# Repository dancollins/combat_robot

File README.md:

## Firmware

### Prerequisites

1. [Miniconda](https://docs.anaconda.com/miniconda/), and an environment with Python 3.10
2. [Zephyr SDK](https://docs.zephyrproject.org/latest/develop/toolchains/zephyr_sdk.html)
3. [CMake](https://cmake.org/download/)
4. [Ninja](https://ninja-build.org/)

Now you can run a few commands to get more dependancies:

    cd <repo>/zephyr-workspace
    west update
    cd zephyr/scripts
    pip install -r requirements.txt
    cd <repo>/zephyr-workspace

### Building

There's no actual firmware or board yet - so in the mean time here's a generic
build for the included minimal sample.

    west build --pristine --board nucleo_l412rb_p firmware

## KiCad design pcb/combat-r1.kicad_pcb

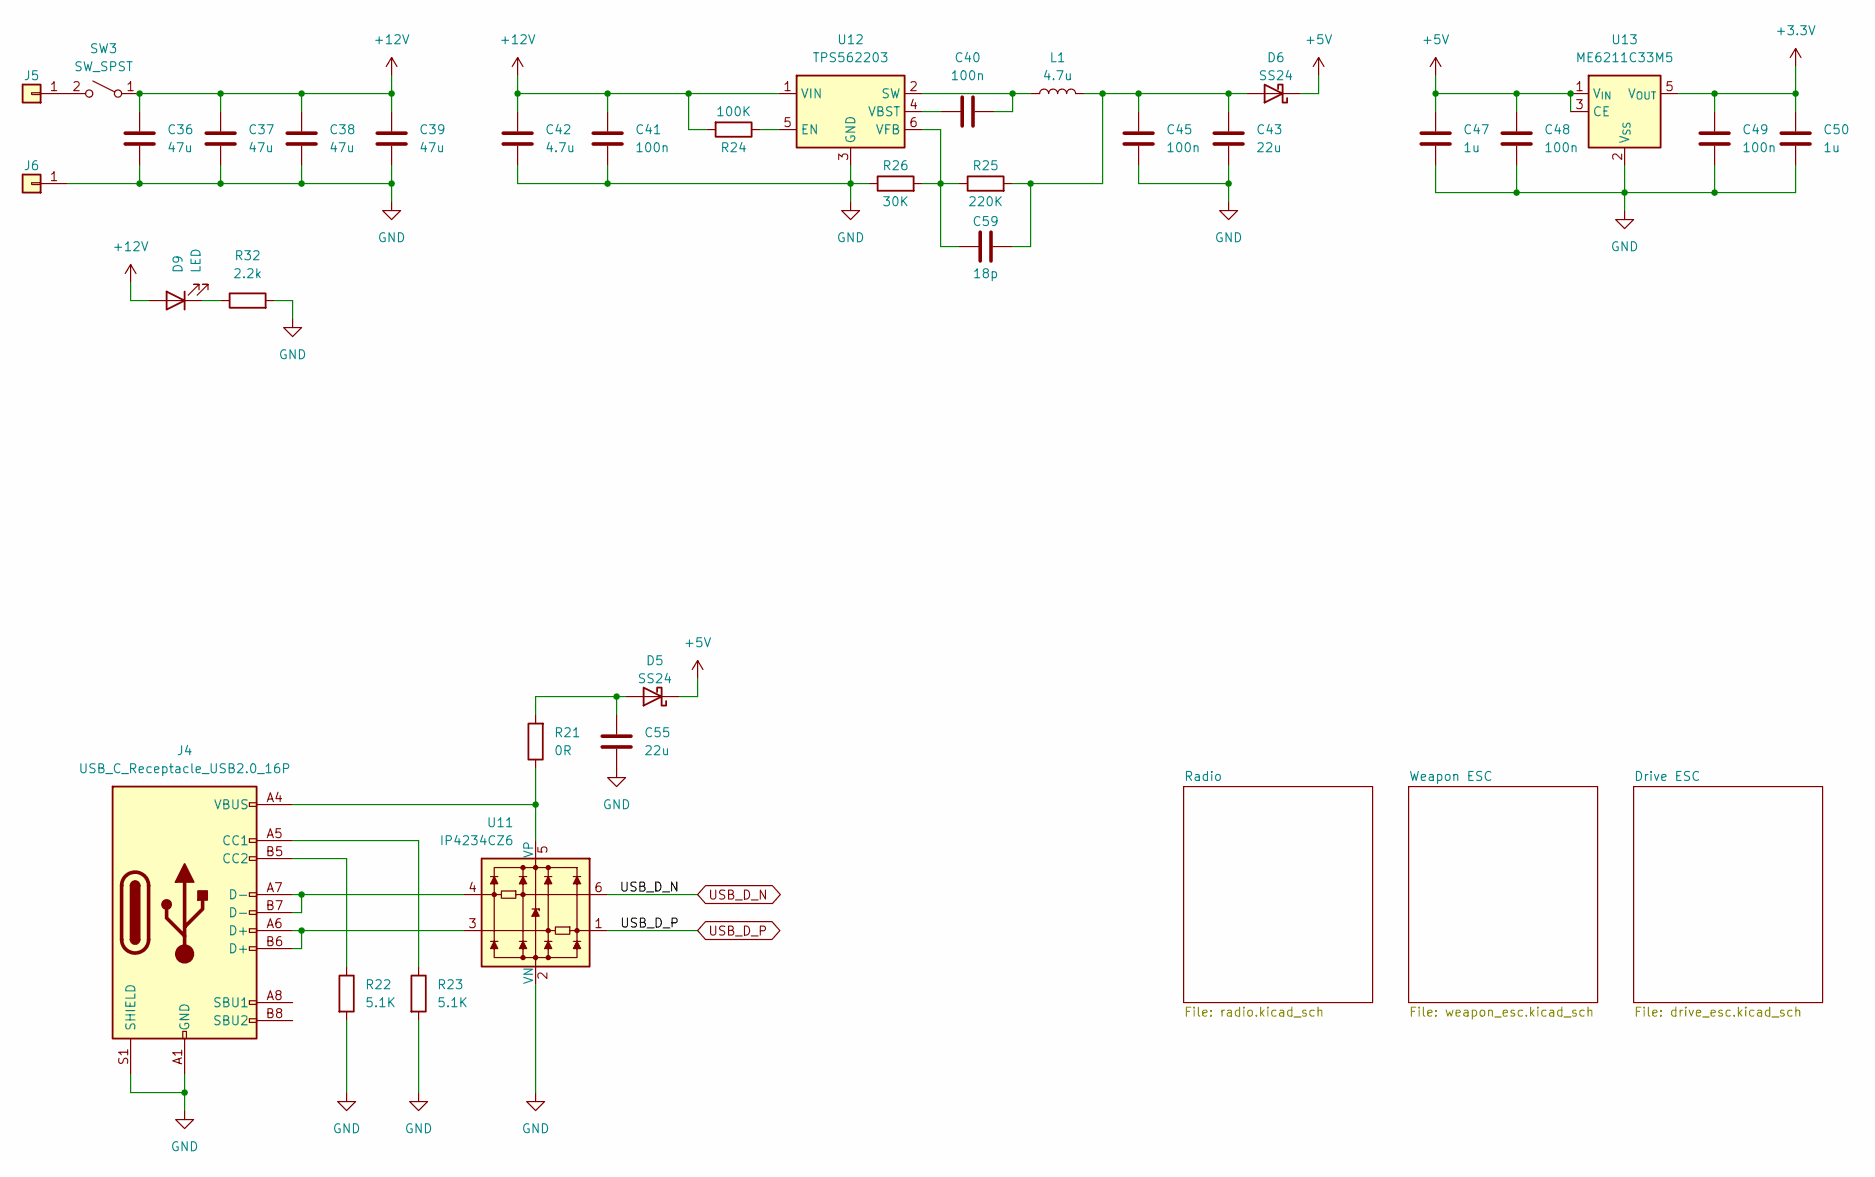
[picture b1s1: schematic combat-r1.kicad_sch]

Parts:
C36, C37, C38, C39: 47u; C_1210_3225Metric; LCSC C90142
C40, C41, C45, C48: 100n; C_0603_1608Metric; LCSC C1591
C42: 4.7u; C_0603_1608Metric; LCSC C69335
C43, C55: 22u; C_0805_2012Metric; LCSC C602037
C47: 1u; C_0603_1608Metric; Voltage 10V; LCSC C29936
C49: 100n; C_0603_1608Metric; Voltage 10V; LCSC C1591
C50: 1u; C_0603_1608Metric; LCSC C29936
C59: 18p; C_0603_1608Metric; LCSC C1647
D5, D6: SS24; D_SMA; LCSC C6069590
D9: LED; LED_0603_1608Metric; LCSC C434425
J4: USB_C_Receptacle_USB2.0_16P; USB_C_Receptacle_GCT_USB4105-xx-A_16P_TopMnt_Horizontal; LCSC C165948
J5, J6: Conn_01x01; SolderWire-1sqmm_1x01_D1.4mm_OD3.9mm
L1: 4.7u; L_Sunlord_MWSA0624S; LCSC C408433
R21: 0R; R_0603_1608Metric; LCSC C21189
R22, R23: 5.1K; R_0603_1608Metric; LCSC C23186
R24: 100K; R_0603_1608Metric; LCSC C25803
R25: 220K; R_0603_1608Metric; LCSC C22961
R26: 30K; R_0603_1608Metric; LCSC C22984
R32: 2.2k; R_0603_1608Metric; LCSC C4190
SW3: SW_SPST; m3-power-switch; LCSC C7528081
U11: IP4234CZ6; SC-74-6_1.55x2.9mm_P0.95mm; LCSC C551509
U12: TPS562203; SOT-563; LCSC C22445511
U13: ME6211C33M5; SOT-23-5; LCSC C82942

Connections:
+3.3V: C49.1, C50.1, U13.5 (V_{OUT}); also elsewhere on the board
+5V: C47.1, C48.1, D5.1 (K), D6.1 (K), U13.1 (V_{IN}), U13.3 (CE)
+12V: C36.1, C37.1, C38.1, C39.1, C41.1, C42.1, D9.2 (A), R24.2, SW3.1 (A), U12.1 (VIN); also elsewhere on the board
GND: C36.2, C37.2, C38.2, C39.2, C41.2, C42.2, C43.2, C45.2, C47.2, C48.2, C49.2, C50.2, C55.2, J4.A1 (GND), J4.A12 (GND), J4.B1 (GND), J4.B12 (GND), J4.S1 (SHIELD), J6.1, R22.2, R23.2, R26.1, R32.2, U11.2 (VN), U12.3 (GND), U13.2 (V_{SS}); also elsewhere on the board
unnamed: C55.1, D5.2 (A), R21.2
unnamed: C43.1, C45.1, C59.1, D6.2 (A), L1.2, R25.2
unnamed: D9.1 (K), R32.1
unnamed: J4.A5 (CC1), R23.1
unnamed: J4.B5 (CC2), R22.1
unnamed: J4.A6 (D+), J4.B6 (D+), U11.3
unnamed: J4.A7 (D-), J4.B7 (D-), U11.4
unnamed: J5.1, SW3.2 (B)
unnamed: J4.A4 (VBUS), J4.A9 (VBUS), J4.B4 (VBUS), J4.B9 (VBUS), R21.1, U11.5 (VP)
unnamed: R24.1, U12.5 (EN)
unnamed: C40.1, L1.1, U12.2 (SW)
unnamed: C40.2, U12.4 (VBST)
unnamed: C59.2, R25.1, R26.2, U12.6 (VFB)
USB_D_N: U11.6; also elsewhere on the board
USB_D_P: U11.1; also elsewhere on the board

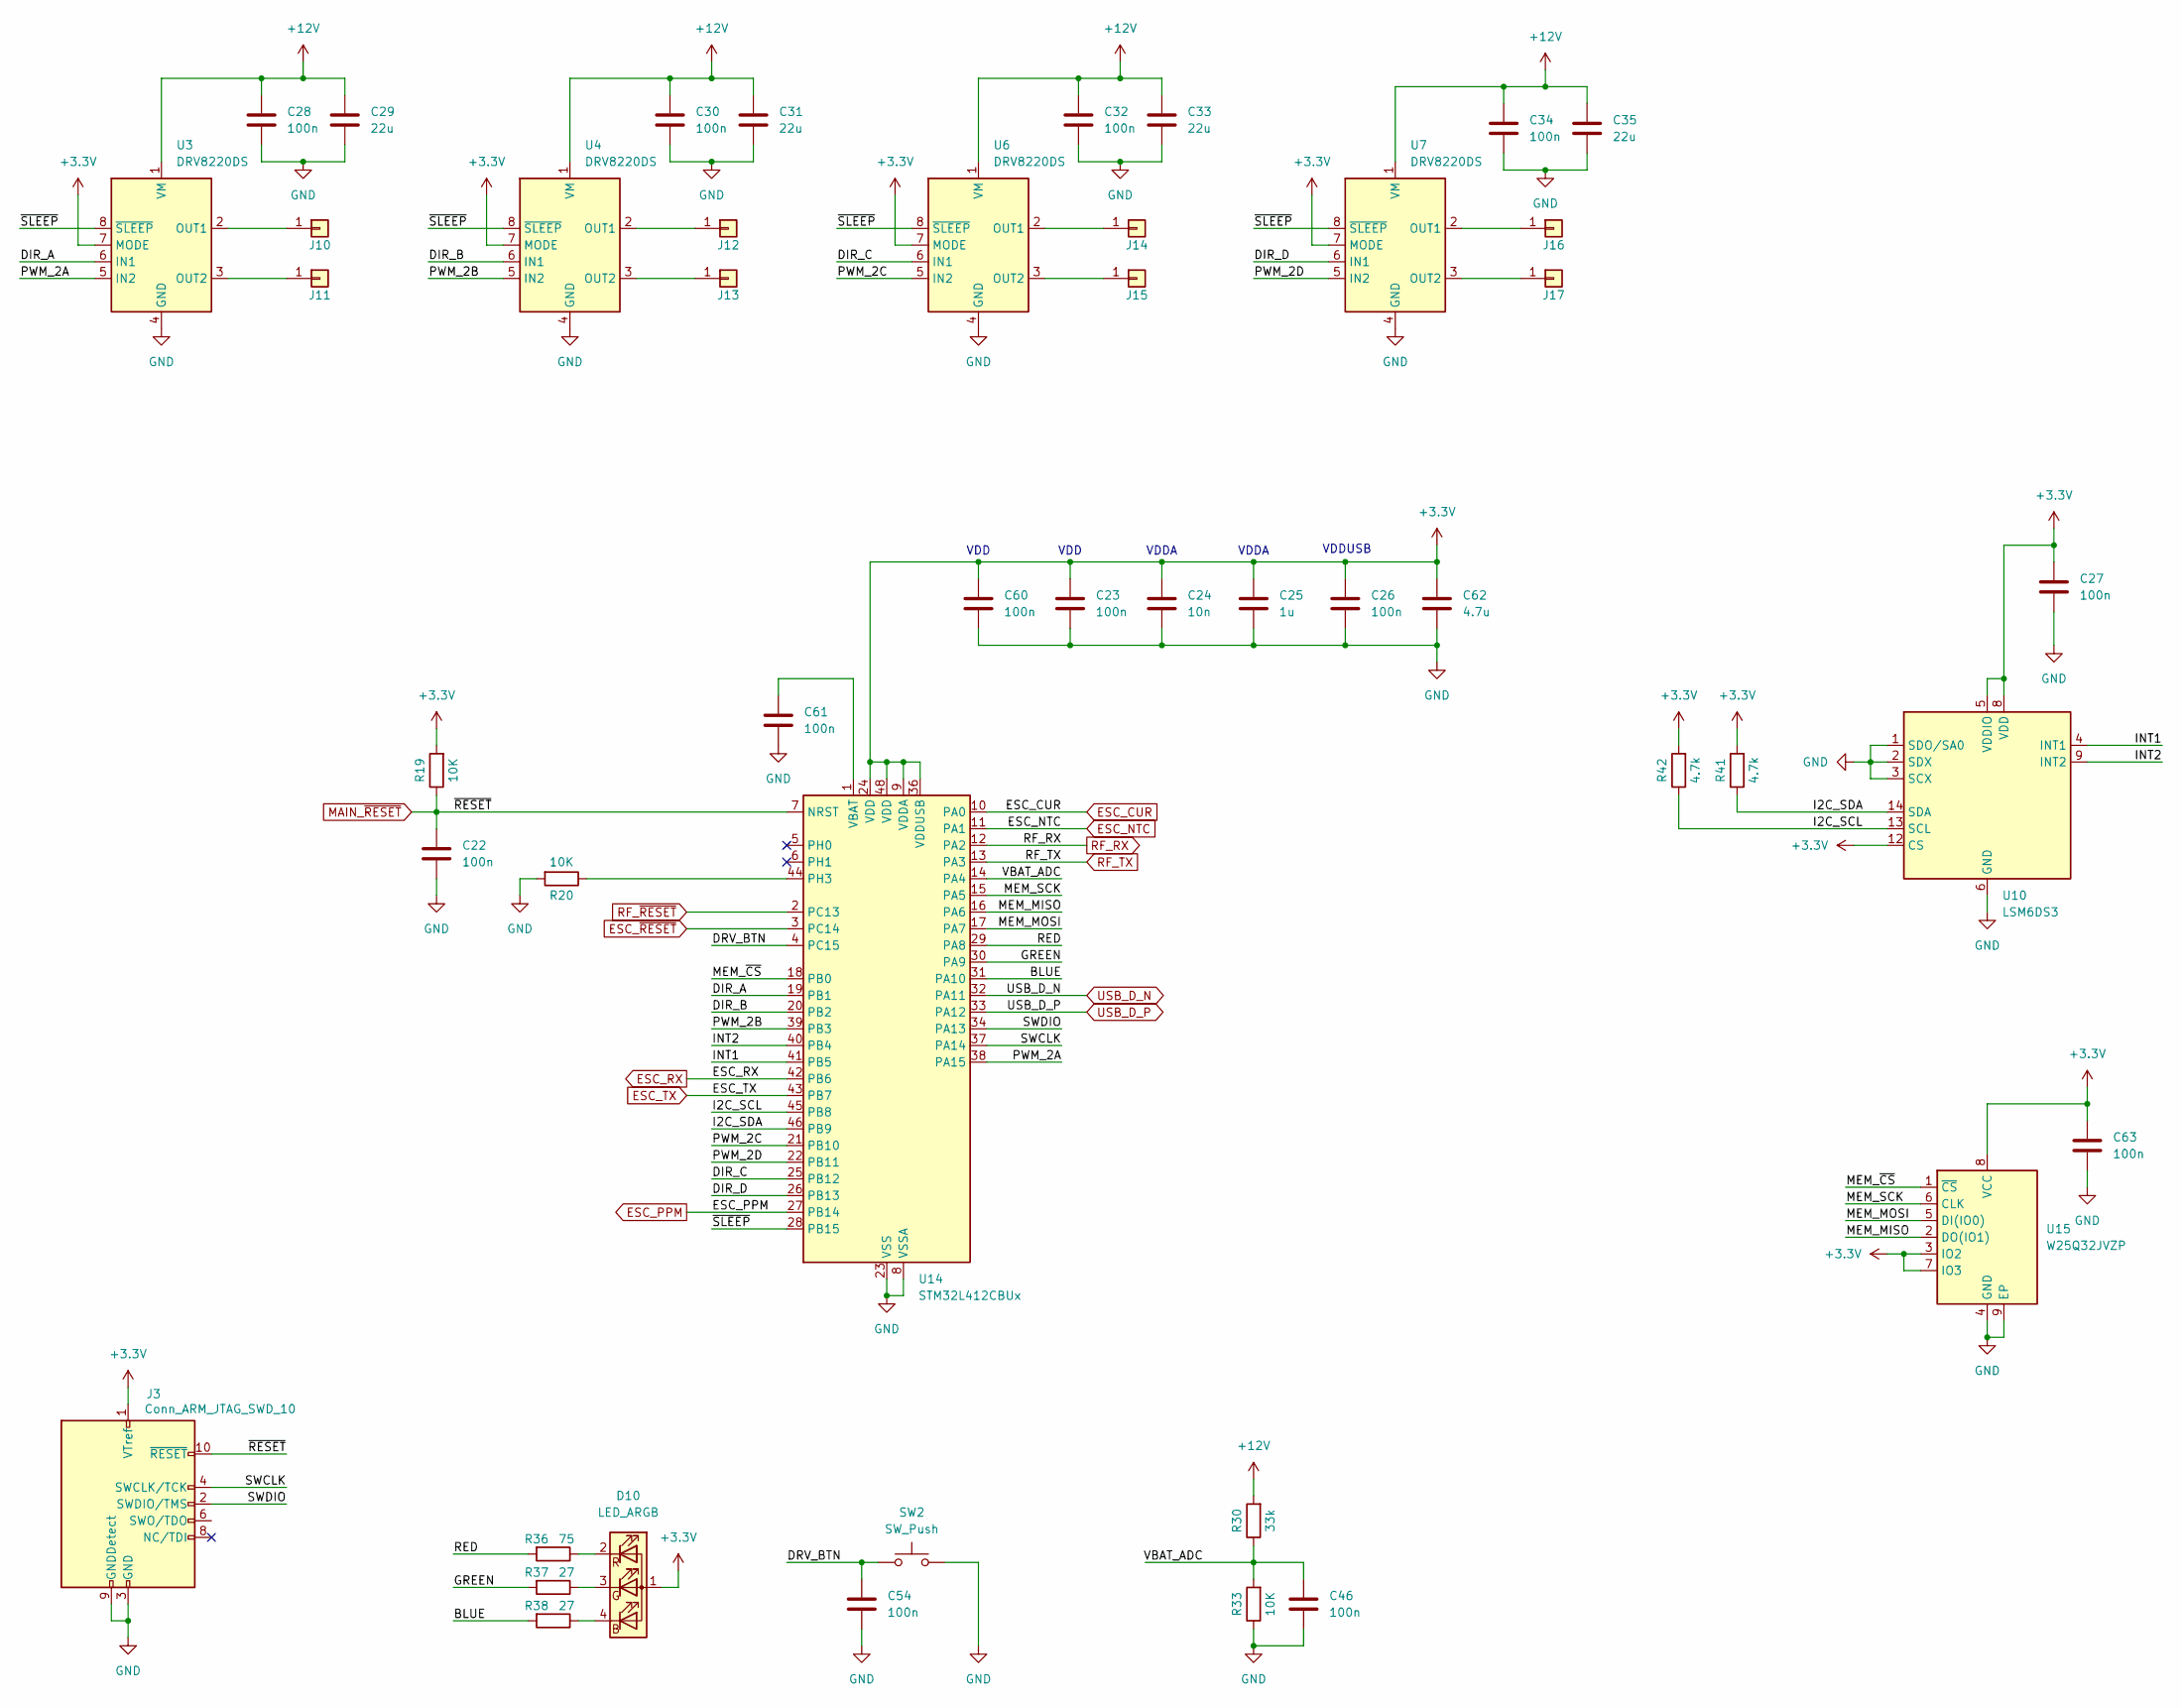
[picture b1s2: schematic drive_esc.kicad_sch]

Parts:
C22, C23, C26, C27, C28, C30, C32, C34, C46, C54, C60, C61, C63: 100n; C_0603_1608Metric; LCSC C1591
C24: 10n; C_0603_1608Metric; LCSC C1589
C25: 1u; C_0603_1608Metric; LCSC C29936
C29, C31, C33, C35: 22u; C_1206_3216Metric; LCSC C342620
C62: 4.7u; C_0603_1608Metric; LCSC C69335
D10: LED_ARGB; LED_LiteOn_LTST-C19HE1WT; LCSC C458749
J3: Conn_ARM_JTAG_SWD_10; PinHeader_2x05_P1.27mm_Vertical_SMD
J10, J11, J12, J13, J14, J15, J16, J17: Conn_01x01; SolderWire-1sqmm_1x01_D1.4mm_OD3.9mm
R19, R20, R33: 10K; R_0603_1608Metric; LCSC C25804
R30: 33k; R_0603_1608Metric; LCSC C4216
R36: 75; R_0603_1608Metric; LCSC C4275
R37, R38: 27; R_0603_1608Metric; LCSC C25190
R41, R42: 4.7k; R_0603_1608Metric; LCSC C23162
SW2: SW_Push; SW_SPST_Omron_B3FS-100xP; LCSC C4364467
U3, U4, U6, U7: DRV8220DS; WSON-8-1EP_2x2mm_P0.5mm_EP0.9x1.6mm; LCSC C3681269
U10: LSM6DS3; LGA-14_3x2.5mm_P0.5mm_LayoutBorder3x4y; LCSC C95230
U14: STM32L412CBUx; QFN-48-1EP_7x7mm_P0.5mm_EP5.6x5.6mm; Mouser 511-STM32L412C8U6
U15: W25Q32JVZP; WSON-8-1EP_6x5mm_P1.27mm_EP3.4x4.3mm; LCSC C571260

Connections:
+3.3V: C23.1, C24.1, C25.1, C26.1, C27.1, C60.1, C62.1, C63.1, D10.1 (A), J3.1 (VTref), R19.2, R41.2, R42.2, U3.7 (MODE), U4.7 (MODE), U6.7 (MODE), U7.7 (MODE), U10.5 (VDDIO), U10.8 (VDD), U10.12 (CS), U14.9 (VDDA), U14.24 (VDD), U14.36 (VDDUSB), U14.48 (VDD), U15.3 (IO2), U15.7 (IO3), U15.8 (VCC); also elsewhere on the board
+12V: C28.1, C29.1, C30.1, C31.1, C32.1, C33.1, C34.1, C35.1, R30.2, U3.1 (VM), U4.1 (VM), U6.1 (VM), U7.1 (VM); also elsewhere on the board
/Drive ESC/BLUE: R38.2, U14.31 (PA10)
/Drive ESC/DIR_A: U3.6 (IN1), U14.19 (PB1)
/Drive ESC/DIR_B: U4.6 (IN1), U14.20 (PB2)
/Drive ESC/DIR_C: U6.6 (IN1), U14.25 (PB12)
/Drive ESC/DIR_D: U7.6 (IN1), U14.26 (PB13)
/Drive ESC/DRV_BTN: C54.1, SW2.1, U14.4 (PC15)
/Drive ESC/GREEN: R37.2, U14.30 (PA9)
/Drive ESC/I2C_SCL: R42.1, U10.13 (SCL), U14.45 (PB8)
/Drive ESC/I2C_SDA: R41.1, U10.14 (SDA), U14.46 (PB9)
/Drive ESC/INT1: U10.4 (INT1), U14.41 (PB5)
/Drive ESC/INT2: U10.9 (INT2), U14.40 (PB4)
/Drive ESC/MEM_MISO: U14.16 (PA6), U15.2 (DO(IO1))
/Drive ESC/MEM_MOSI: U14.17 (PA7), U15.5 (DI(IO0))
/Drive ESC/MEM_SCK: U14.15 (PA5), U15.6 (CLK)
/Drive ESC/MEM_~CS: U14.18 (PB0), U15.1 (~CS)
/Drive ESC/PWM_2A: U3.5 (IN2), U14.38 (PA15)
/Drive ESC/PWM_2B: U4.5 (IN2), U14.39 (PB3)
/Drive ESC/PWM_2C: U6.5 (IN2), U14.21 (PB10)
/Drive ESC/PWM_2D: U7.5 (IN2), U14.22 (PB11)
/Drive ESC/RED: R36.2, U14.29 (PA8)
/Drive ESC/SWCLK: J3.4 (SWCLK/TCK), U14.37 (PA14)
/Drive ESC/SWDIO: J3.2 (SWDIO/TMS), U14.34 (PA13)
/Drive ESC/VBAT_ADC: C46.1, R30.1, R33.2, U14.14 (PA4)
/Drive ESC/~SLEEP: U3.8 (~SLEEP), U4.8 (~SLEEP), U6.8 (~SLEEP), U7.8 (~SLEEP), U14.28 (PB15)
ESC_CUR: U14.10 (PA0); also elsewhere on the board
ESC_NTC: U14.11 (PA1); also elsewhere on the board
ESC_PPM: U14.27 (PB14); also elsewhere on the board
ESC_RX: U14.42 (PB6); also elsewhere on the board
ESC_TX: U14.43 (PB7); also elsewhere on the board
ESC_~RESET: U14.3 (PC14); also elsewhere on the board
GND: C22.2, C23.2, C24.2, C25.2, C26.2, C27.2, C28.2, C29.2, C30.2, C31.2, C32.2, C33.2, C34.2, C35.2, C46.2, C54.2, C60.2, C61.2, C62.2, C63.2, J3.3 (GND), J3.5 (GND), J3.9 (GNDDetect), R20.2, R33.1, SW2.2, U3.4 (GND), U3.9 (GND), U4.4 (GND), U4.9 (GND), U6.4 (GND), U6.9 (GND), U7.4 (GND), U7.9 (GND), U10.1 (SDO/SA0), U10.2 (SDX), U10.3 (SCX), U10.6 (GND), U10.7 (GND), U14.8 (VSSA), U14.23 (VSS), U14.35 (VSS), U14.47 (VSS), U14.49 (VSS), U15.4 (GND), U15.9 (EP); also elsewhere on the board
MAIN_~RESET: C22.1, J3.10 (~RESET), R19.1, U14.7 (NRST)
unnamed: D10.4 (BK), R38.1
unnamed: D10.3 (GK), R37.1
unnamed: D10.2 (RK), R36.1
unnamed: J10.1, U3.2 (OUT1)
unnamed: J11.1, U3.3 (OUT2)
unnamed: J12.1, U4.2 (OUT1)
unnamed: J13.1, U4.3 (OUT2)
unnamed: J14.1, U6.2 (OUT1)
unnamed: J15.1, U6.3 (OUT2)
unnamed: J16.1, U7.2 (OUT1)
unnamed: J17.1, U7.3 (OUT2)
unnamed: R20.1, U14.44 (PH3)
unnamed: C61.1, U14.1 (VBAT)
RF_RX: U14.12 (PA2); also elsewhere on the board
RF_TX: U14.13 (PA3); also elsewhere on the board
RF_~RESET: U14.2 (PC13); also elsewhere on the board
USB_D_N: U14.32 (PA11); also elsewhere on the board
USB_D_P: U14.33 (PA12); also elsewhere on the board

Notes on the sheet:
VDDUSB
VDDA
VDD

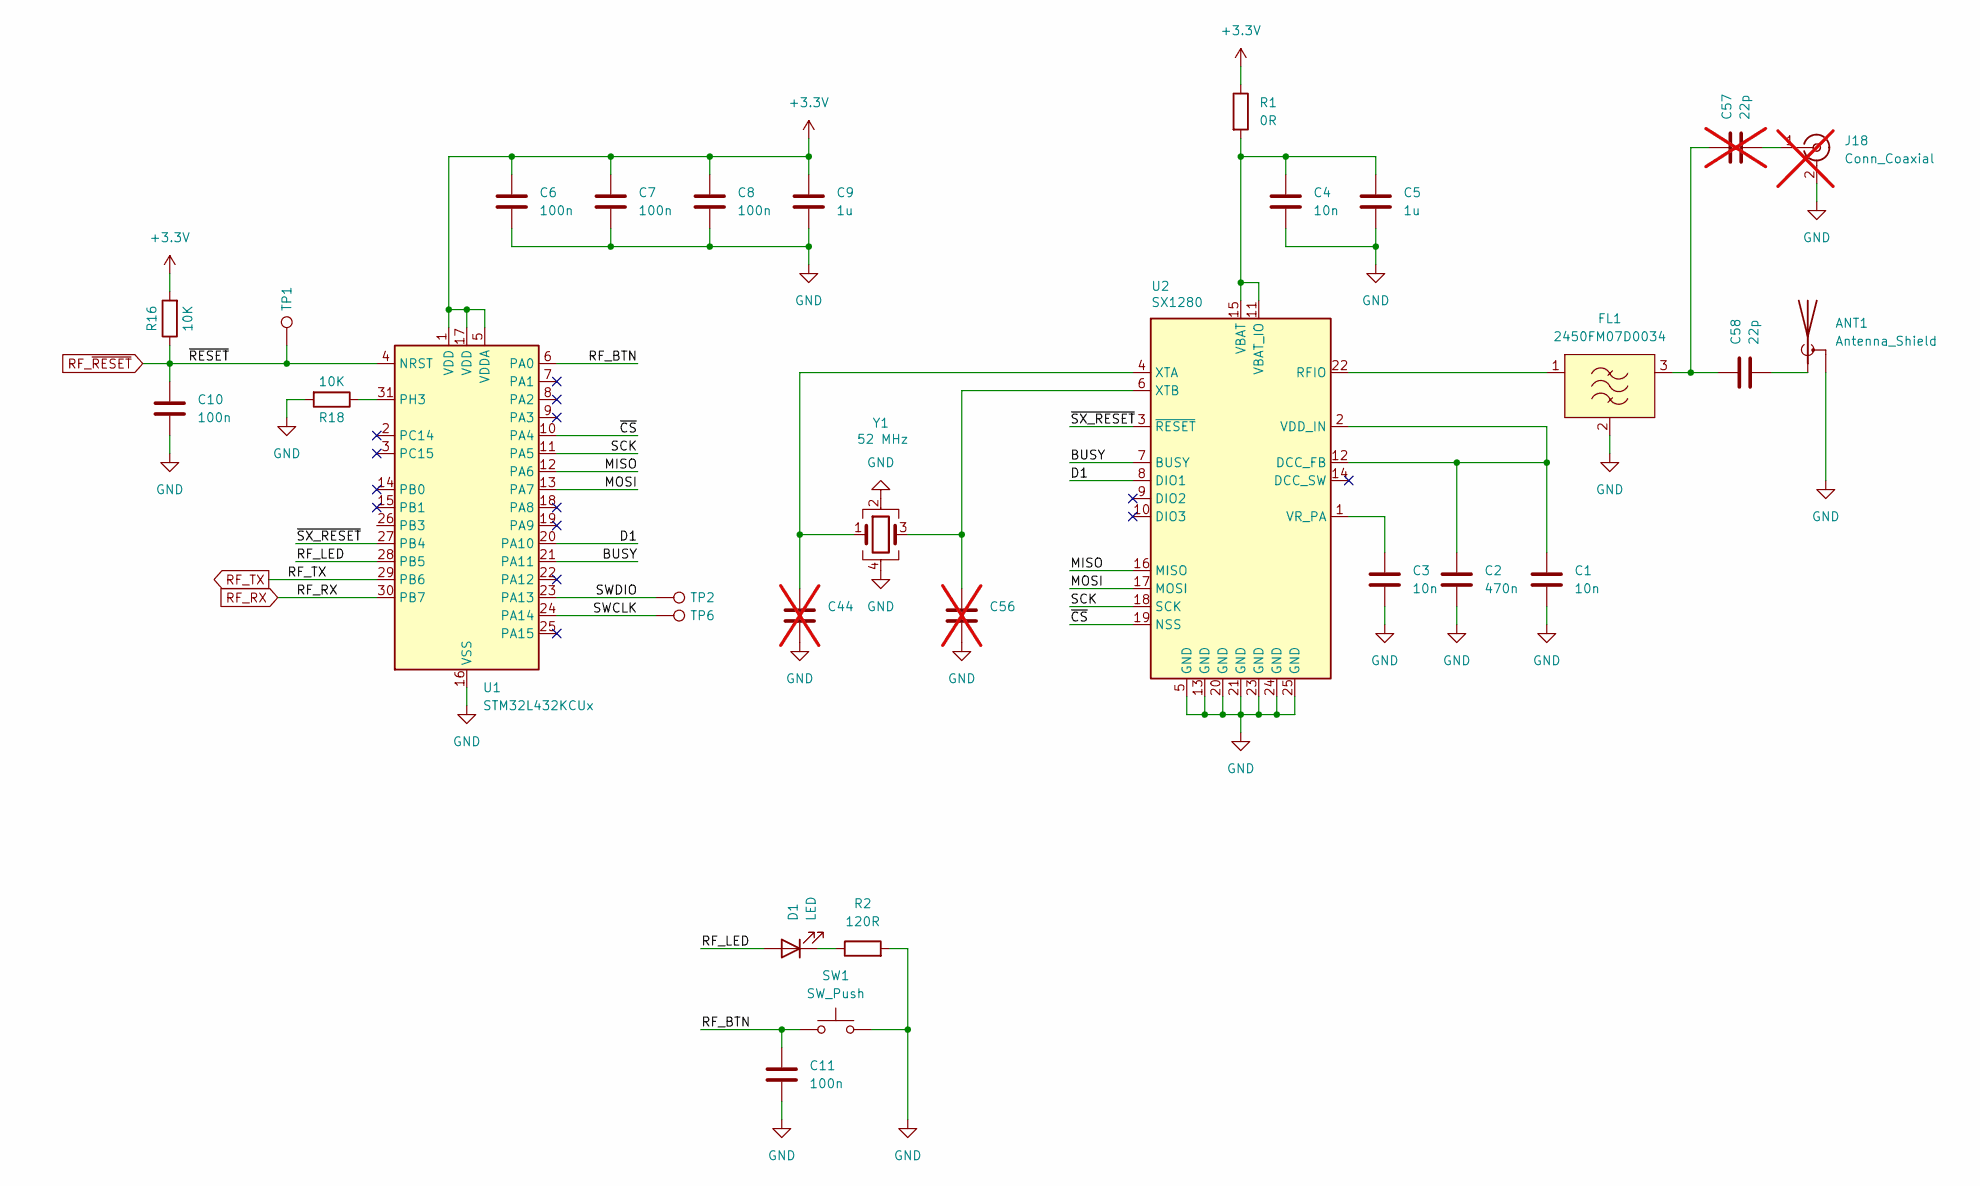
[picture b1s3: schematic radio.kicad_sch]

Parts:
ANT1: Antenna_Shield; Texas_SWRA117D_2.4GHz_Left
C1, C3, C4: 10n; C_0603_1608Metric; LCSC C1589
C2: 470n; C_0603_1608Metric; LCSC C1623
C5, C9: 1u; C_0603_1608Metric; LCSC C29936
C6, C7, C8, C10, C11: 100n; C_0603_1608Metric; LCSC C1591
C44, C56: C_0603_1608Metric; not fitted
C57: 22p; C_0603_1608Metric; LCSC C1653; not fitted
C58: 22p; C_0603_1608Metric; LCSC C1653
D1: LED; LED_0603_1608Metric; LCSC C965804
FL1: 2450FM07D0034; LCSC C2651081
J18: Conn_Coaxial; U.FL_Molex_MCRF_73412-0110_Vertical; LCSC C88374; not fitted
R1: 0R; R_0603_1608Metric; LCSC C21189
R2: 120R; R_0603_1608Metric; LCSC C22787
R16, R18: 10K; R_0603_1608Metric; LCSC C25804
SW1: SW_Push; SW_SPST_Omron_B3FS-100xP; LCSC C4364467
TP1, TP2, TP6: TestPoint; TestPoint_Pad_D2.0mm
U1: STM32L432KCUx; QFN-32-1EP_5x5mm_P0.5mm_EP3.45x3.45mm; LCSC C1337280
U2: SX1280; QFN-24-1EP_4x4mm_P0.5mm_EP2.7x2.7mm; LCSC C125969
Y1: 52 MHz; Crystal_SMD_2016-4Pin_2.0x1.6mm; LCSC C1986193

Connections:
+3.3V: C6.1, C7.1, C8.1, C9.1, R1.1, R16.2, U1.1 (VDD), U1.5 (VDDA), U1.17 (VDD); also elsewhere on the board
/Radio/BUSY: U1.21 (PA11), U2.7 (BUSY)
/Radio/D1: U1.20 (PA10), U2.8 (DIO1)
/Radio/MISO: U1.12 (PA6), U2.16 (MISO)
/Radio/MOSI: U1.13 (PA7), U2.17 (MOSI)
/Radio/RF_BTN: C11.1, SW1.1, U1.6 (PA0)
/Radio/RF_LED: D1.2 (A), U1.28 (PB5)
/Radio/SCK: U1.11 (PA5), U2.18 (SCK)
/Radio/SWCLK: TP6.1, U1.24 (PA14)
/Radio/SWDIO: TP2.1, U1.23 (PA13)
/Radio/~CS: U1.10 (PA4), U2.19 (NSS)
/Radio/~SX_RESET: U1.27 (PB4), U2.3 (~RESET)
GND: ANT1.2 (Shield), C1.2, C2.2, C3.2, C4.2, C5.2, C6.2, C7.2, C8.2, C9.2, C10.2, C11.2, C44.2, C56.2, FL1.2 (GND), FL1.4 (GND), J18.2 (Ext), R2.2, R18.2, SW1.2, U1.16 (VSS), U1.32 (VSS), U1.33 (VSS), U2.5 (GND), U2.13 (GND), U2.20 (GND), U2.21 (GND), U2.23 (GND), U2.24 (GND), U2.25 (GND), Y1.2, Y1.4; also elsewhere on the board
unnamed: ANT1.1 (A), C58.2
unnamed: D1.1 (K), R2.1
unnamed: FL1.1 (RF_IN), U2.22 (RFIO)
unnamed: C57.1, C58.1, FL1.3 (RF_OUT)
unnamed: C57.2, J18.1 (In)
unnamed: R18.1, U1.31 (PH3)
unnamed: C1.1, C2.1, U2.2 (VDD_IN), U2.12 (DCC_FB)
unnamed: C4.1, C5.1, R1.2, U2.11 (VBAT_IO), U2.15 (VBAT)
unnamed: C3.1, U2.1 (VR_PA)
unnamed: C44.1, U2.4 (XTA), Y1.1
unnamed: C56.1, U2.6 (XTB), Y1.3
RF_RX: U1.30 (PB7); also elsewhere on the board
RF_TX: U1.29 (PB6); also elsewhere on the board
RF_~RESET: C10.1, R16.1, TP1.1, U1.4 (NRST); also elsewhere on the board

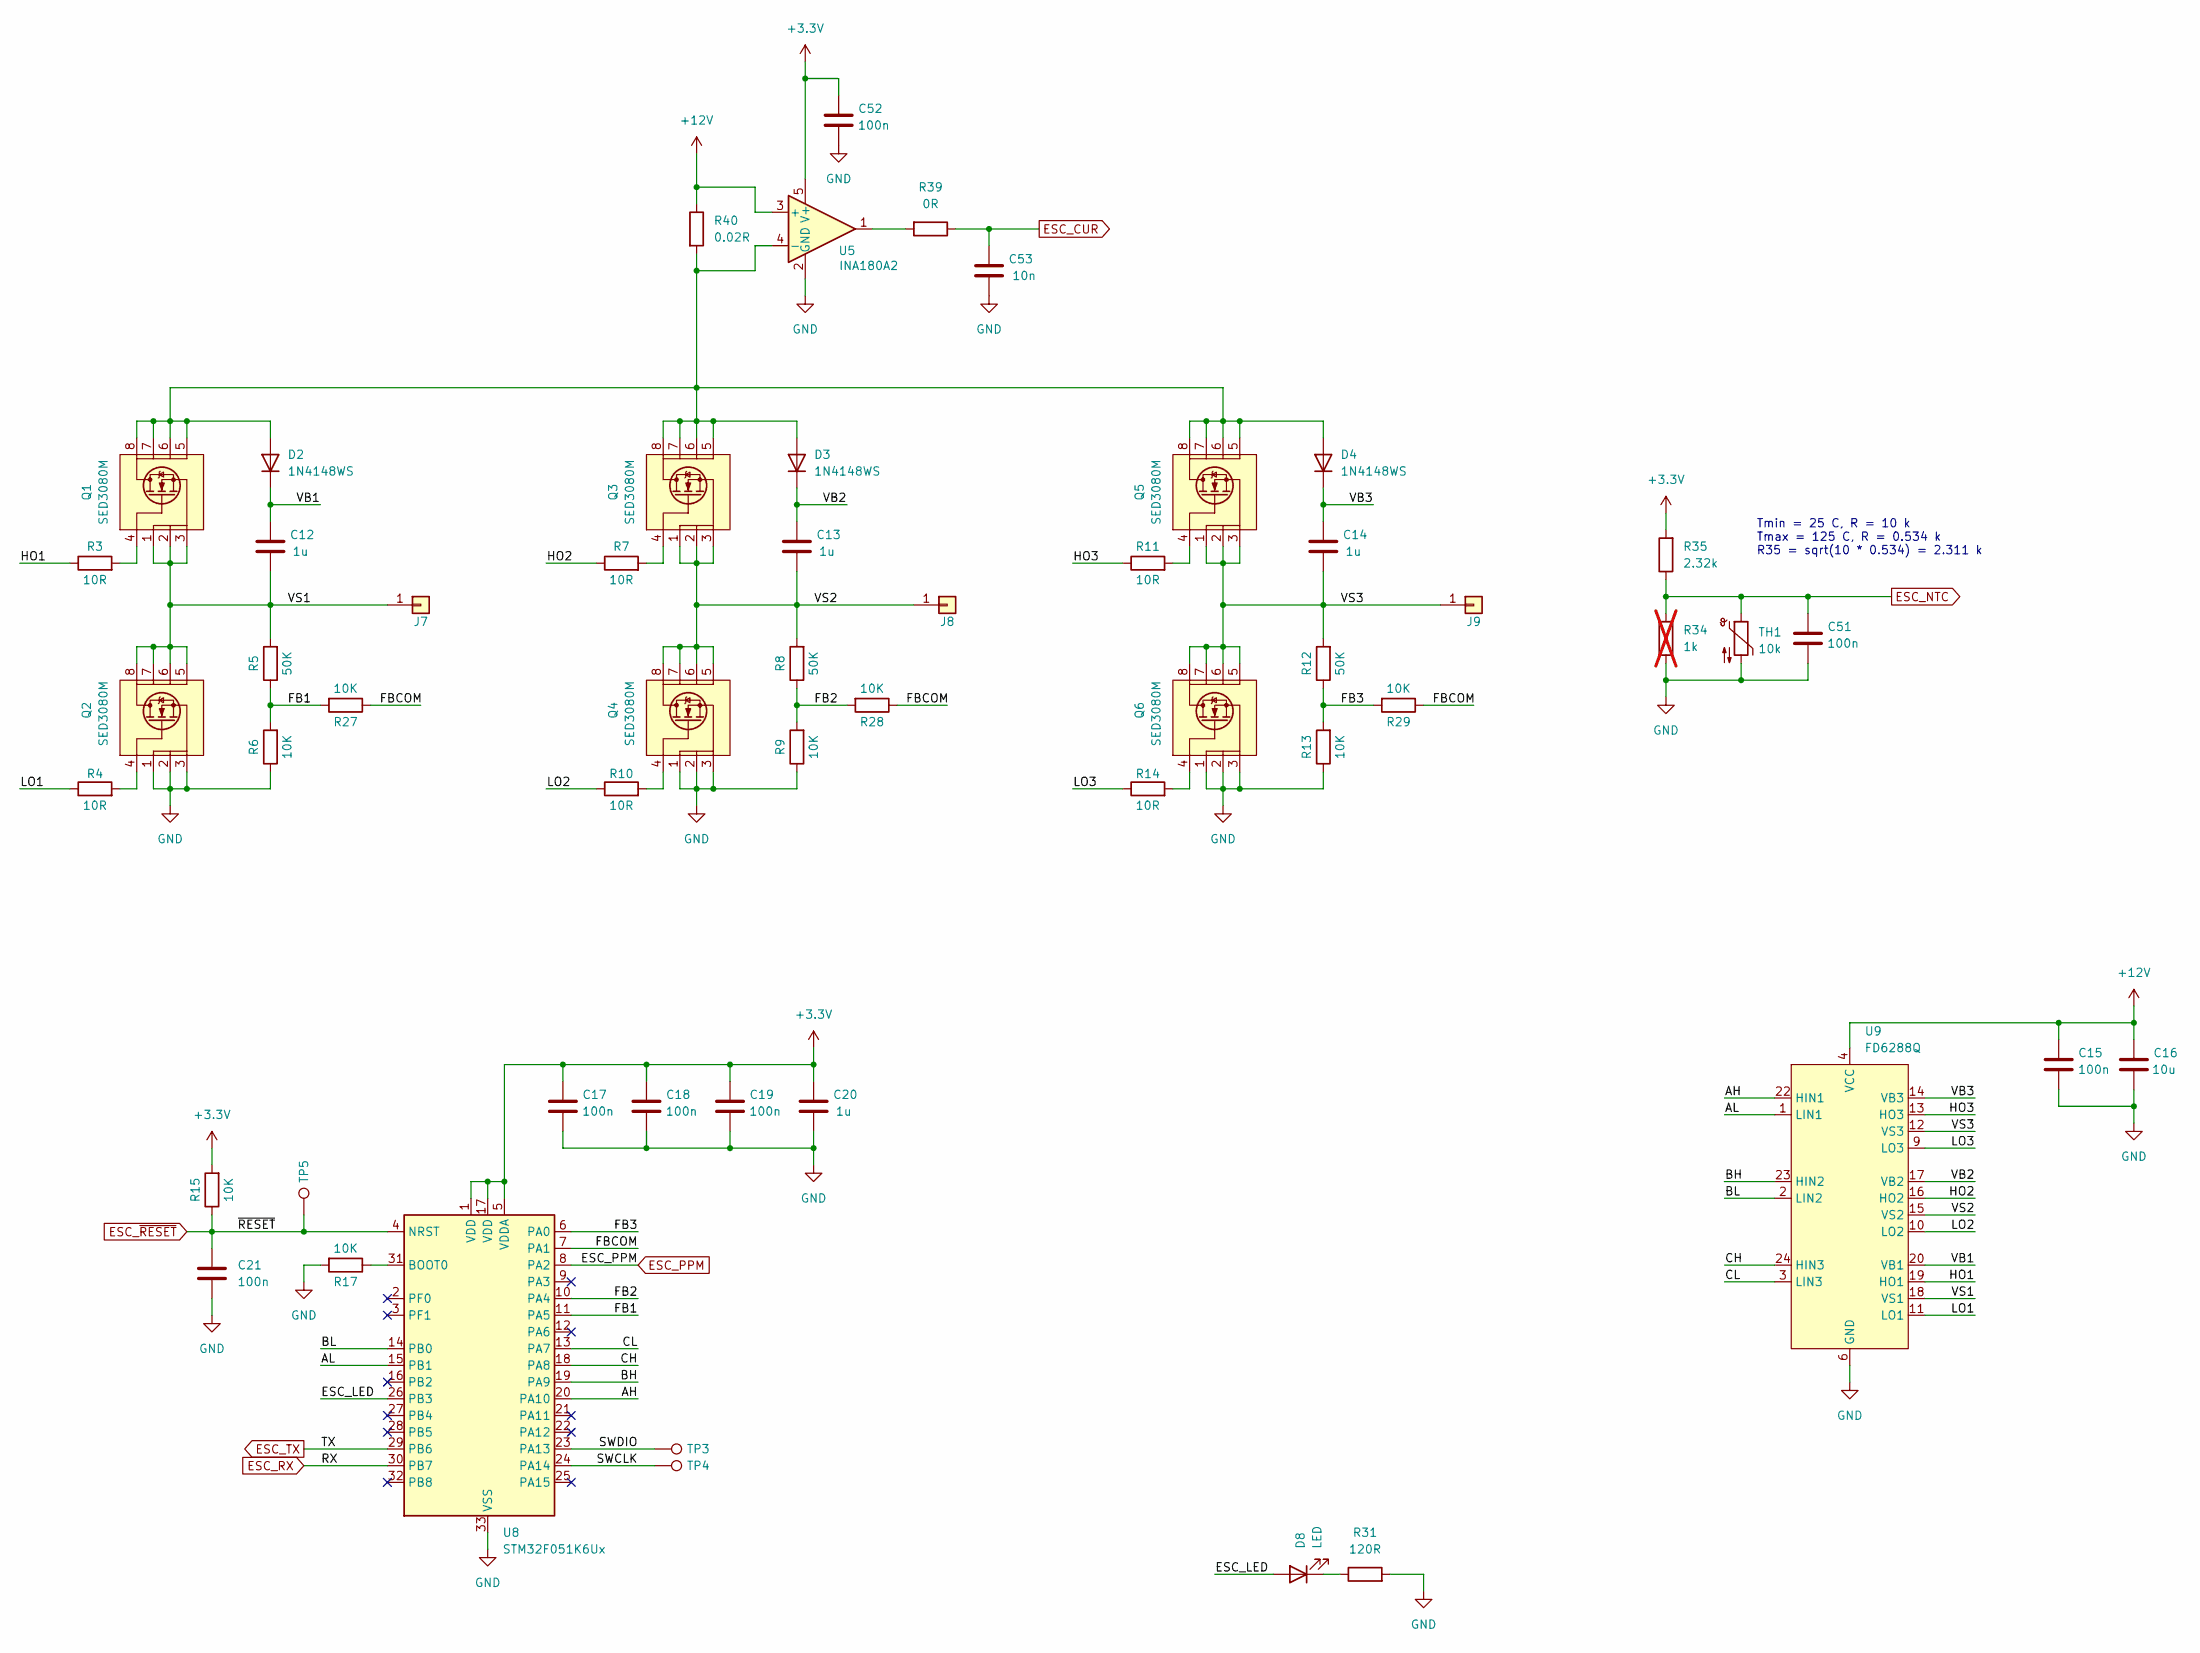
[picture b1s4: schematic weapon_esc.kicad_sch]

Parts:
C12, C13, C14, C20: 1u; C_0603_1608Metric; LCSC C29936
C15, C17, C18, C19, C21, C51, C52: 100n; C_0603_1608Metric; LCSC C1591
C16: 10u; C_0805_2012Metric; LCSC C440198
C53: 10n; C_0603_1608Metric; LCSC C1589
D2, D3, D4: 1N4148WS; D_SOD-323; LCSC C435854
D8: LED; LED_0603_1608Metric; LCSC C965804
J7, J8, J9: Conn_01x01; SolderWire-1sqmm_1x01_D1.4mm_OD3.9mm
Q1, Q2, Q3, Q4, Q5, Q6: SED3080M; DFN-8-SED3080M; LCSC C238667
R3, R4, R7, R10, R11, R14: 10R; R_0603_1608Metric; LCSC C22859
R5, R8, R12: 50K; R_0603_1608Metric; LCSC C304067
R6, R9, R13, R15, R17, R27, R28, R29: 10K; R_0603_1608Metric; LCSC C25804
R31: 120R; R_0603_1608Metric; LCSC C22787
R34: 1k; R_0603_1608Metric; LCSC C21190; not fitted
R35: 2.32k; R_0603_1608Metric; LCSC C22905
R39: 0R; R_0603_1608Metric; LCSC C21189
R40: 0.02R; R_1206_3216Metric; LCSC C723441
TH1: 10k; R_0603_1608Metric; LCSC C76589
TP3, TP4, TP5: TestPoint; TestPoint_Pad_D2.0mm
U5: INA180A2; SOT-23-5; LCSC C192764
U8: STM32F051K6Ux; QFN-32-1EP_5x5mm_P0.5mm_EP3.45x3.45mm; LCSC C81451
U9: FD6288Q; QFN-24-1EP_4x4mm_P0.5mm_EP2.65x2.65mm; LCSC C328453

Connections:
+3.3V: C17.1, C18.1, C19.1, C20.1, C52.1, R15.2, R35.2, U5.5 (V+), U8.1 (VDD), U8.5 (VDDA), U8.17 (VDD); also elsewhere on the board
+12V: C15.1, C16.1, R40.1, U5.3 (+), U9.4 (VCC); also elsewhere on the board
/Weapon ESC/AH: U8.20 (PA10), U9.22 (HIN1)
/Weapon ESC/AL: U8.15 (PB1), U9.1 (LIN1)
/Weapon ESC/BH: U8.19 (PA9), U9.23 (HIN2)
/Weapon ESC/BL: U8.14 (PB0), U9.2 (LIN2)
/Weapon ESC/CH: U8.18 (PA8), U9.24 (HIN3)
/Weapon ESC/CL: U8.13 (PA7), U9.3 (LIN3)
/Weapon ESC/ESC_LED: D8.2 (A), U8.26 (PB3)
/Weapon ESC/FB1: R5.1, R6.2, R27.2, U8.11 (PA5)
/Weapon ESC/FB2: R8.1, R9.2, R28.2, U8.10 (PA4)
/Weapon ESC/FB3: R12.1, R13.2, R29.2, U8.6 (PA0)
/Weapon ESC/FBCOM: R27.1, R28.1, R29.1, U8.7 (PA1)
/Weapon ESC/HO1: R3.1, U9.19 (HO1)
/Weapon ESC/HO2: R7.1, U9.16 (HO2)
/Weapon ESC/HO3: R11.1, U9.13 (HO3)
/Weapon ESC/LO1: R4.1, U9.11 (LO1)
/Weapon ESC/LO2: R10.1, U9.10 (LO2)
/Weapon ESC/LO3: R14.1, U9.9 (LO3)
/Weapon ESC/SWCLK: TP4.1, U8.24 (PA14)
/Weapon ESC/SWDIO: TP3.1, U8.23 (PA13)
/Weapon ESC/VB1: C12.1, D2.1 (K), U9.20 (VB1)
/Weapon ESC/VB2: C13.1, D3.1 (K), U9.17 (VB2)
/Weapon ESC/VB3: C14.1, D4.1 (K), U9.14 (VB3)
/Weapon ESC/VS1: C12.2, J7.1, Q1.1 (S), Q1.2 (S), Q1.3 (S), Q2.5 (D), Q2.6 (D), Q2.7 (D), Q2.8 (D), Q2.9, R5.2, U9.18 (VS1)
/Weapon ESC/VS2: C13.2, J8.1, Q3.1 (S), Q3.2 (S), Q3.3 (S), Q4.5 (D), Q4.6 (D), Q4.7 (D), Q4.8 (D), Q4.9, R8.2, U9.15 (VS2)
/Weapon ESC/VS3: C14.2, J9.1, Q5.1 (S), Q5.2 (S), Q5.3 (S), Q6.5 (D), Q6.6 (D), Q6.7 (D), Q6.8 (D), Q6.9, R12.2, U9.12 (VS3)
ESC_CUR: C53.1, R39.1; also elsewhere on the board
ESC_NTC: C51.1, R34.2, R35.1, TH1.1; also elsewhere on the board
ESC_PPM: U8.8 (PA2); also elsewhere on the board
ESC_RX: U8.30 (PB7); also elsewhere on the board
ESC_TX: U8.29 (PB6); also elsewhere on the board
ESC_~RESET: C21.1, R15.1, TP5.1, U8.4 (NRST); also elsewhere on the board
GND: C15.2, C16.2, C17.2, C18.2, C19.2, C20.2, C21.2, C51.2, C52.2, C53.2, Q2.1 (S), Q2.2 (S), Q2.3 (S), Q4.1 (S), Q4.2 (S), Q4.3 (S), Q6.1 (S), Q6.2 (S), Q6.3 (S), R6.1, R9.1, R13.1, R17.2, R31.2, R34.1, TH1.2, U5.2 (GND), U8.33 (VSS), U9.6 (GND), U9.25 (GND); also elsewhere on the board
unnamed: D2.2 (A), D3.2 (A), D4.2 (A), Q1.5 (D), Q1.6 (D), Q1.7 (D), Q1.8 (D), Q1.9, Q3.5 (D), Q3.6 (D), Q3.7 (D), Q3.8 (D), Q3.9, Q5.5 (D), Q5.6 (D), Q5.7 (D), Q5.8 (D), Q5.9, R40.2, U5.4 (-)
unnamed: D8.1 (K), R31.1
unnamed: Q1.4 (G), R3.2
unnamed: Q2.4 (G), R4.2
unnamed: Q3.4 (G), R7.2
unnamed: Q4.4 (G), R10.2
unnamed: Q5.4 (G), R11.2
unnamed: Q6.4 (G), R14.2
unnamed: R39.2, U5.1
unnamed: R17.1, U8.31 (BOOT0)

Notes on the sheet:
Tmin = 25 C, R = 10 k Tmax = 125 C, R = 0.534 k R35 = sqrt(10 * 0.534) = 2.311 k

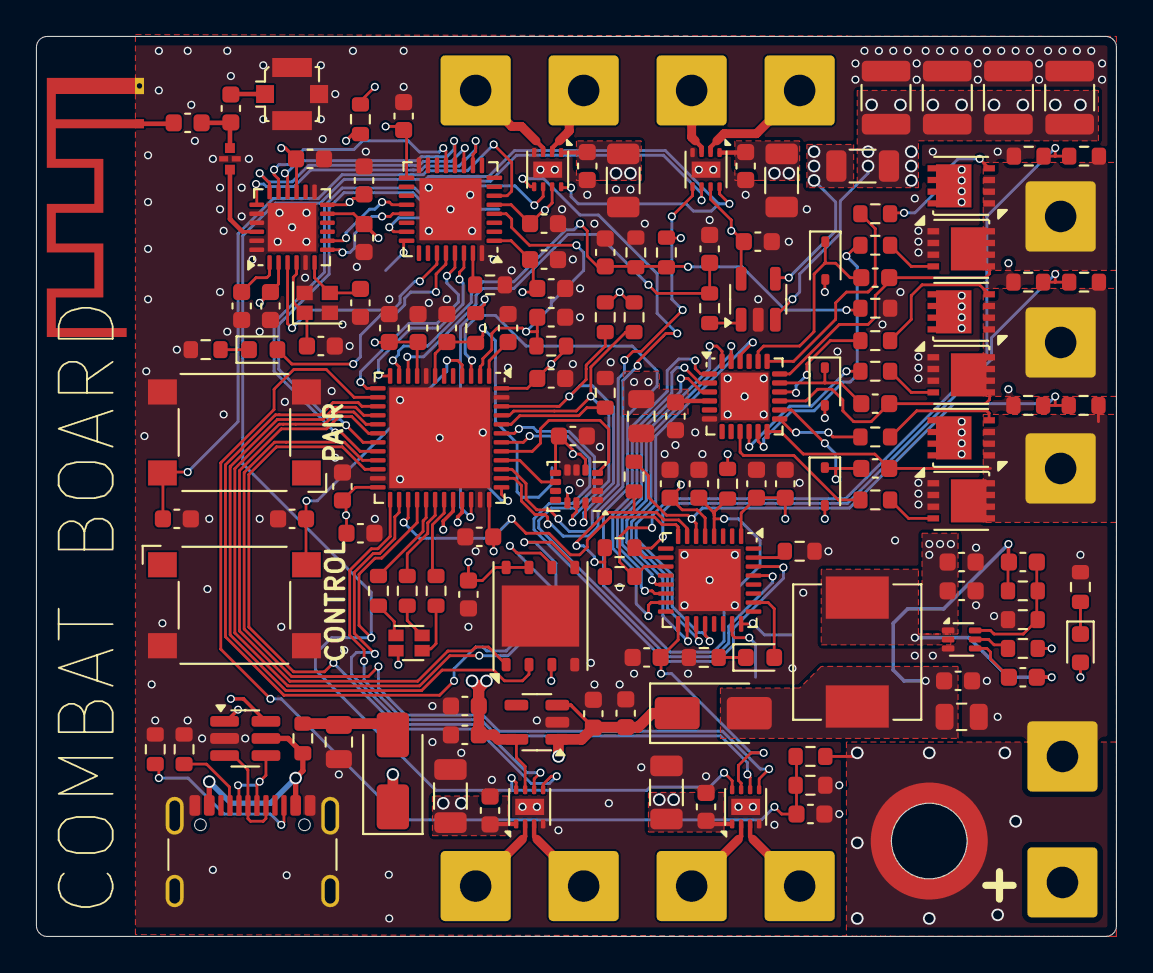
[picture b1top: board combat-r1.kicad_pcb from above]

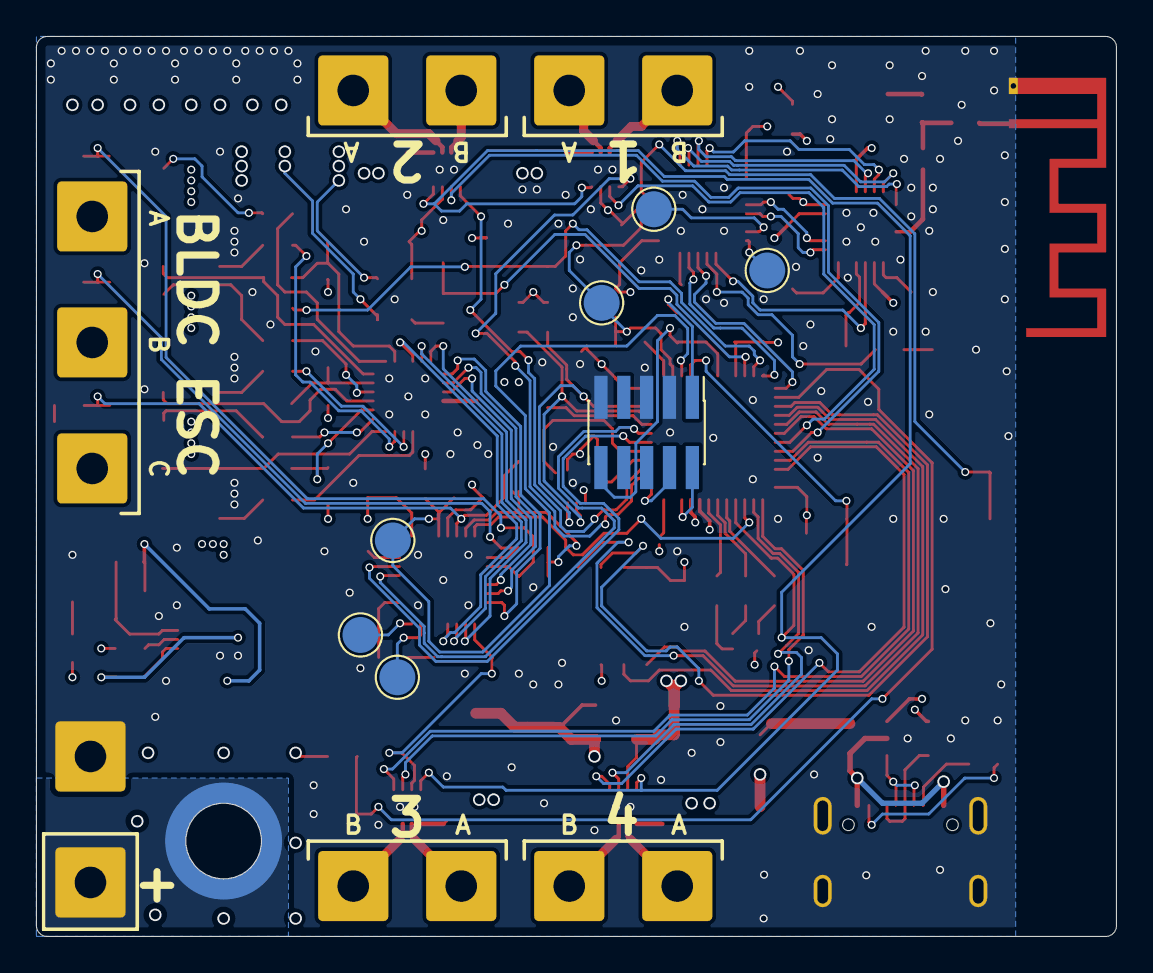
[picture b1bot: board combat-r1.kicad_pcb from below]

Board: 4 copper layers, 60.0 x 50.0 mm, 165 parts (7 on the bottom side), 123 nets.

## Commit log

2024-11-16 initial commit, includes PCB
2024-11-16 Adds ExpressLRS and checks out release with STM32
2024-11-16 Adds AM32 firmware for ESC
2024-11-17 Adds basic Zephyr firmware and required west workspace
2024-11-17 Woops - we're using the L412 for the controller, not the L432
2024-11-18 Adds combat board device tree and updates main to load devices
2024-11-18 adds skeleton for lsm6ds3 driver and littlefs
2024-11-18 Got lsm6ds3tr driver reading device ID
2024-11-18 Dropping littlefs to save about 25k of flash!
    We don't need it - the flash will be used for OTA of the
    radio and esc, and for storing sensor data. None of these
    cases depend on having a filesystem.
2024-11-18 Added tests for RGB LED and flash
2024-11-19 Adds skeleton CSRF driver
    Just prints out received characters. Hopefully enough to
    print data received from the transmitter...
2024-11-24 Runs on real hardware. Flash isn't working though
2024-11-30 finished testing hardware, adds some CSRF decode
    This commit introduces the ESC and DC motor control.
    It also adds some basic frame decoding to the CSRF driver.
2024-11-30 csrf: receives and handles channel data from transmitter!
2024-11-30 app: added channels for DC motor, ESC and the red LED
2024-11-30 app: got channel mixing going - needs testing
    ... but to do that I need a chassis!
2025-06-21 working firmware!
2025-06-21 adds missing files, switches to tank controls
